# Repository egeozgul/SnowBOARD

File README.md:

# SnowBOARD
This open-source prototyping module streamlines embedded system development by eliminating soldering and complex wiring requirements. The module features dedicated connectors and ports that enable plug-and-play peripheral connections through simple socket interfaces, dramatically reducing setup time and complexity.

Key features include an integrated SD card slot for data storage, a comprehensive battery power management circuit for portable applications, a USB Type-C interface for modern connectivity, and a built-in USB-to-UART converter that simplifies debugging and firmware uploads. This design approach makes embedded prototyping more accessible while maintaining professional-grade functionality for developers at all skill levels.

<p align="center">

</p>

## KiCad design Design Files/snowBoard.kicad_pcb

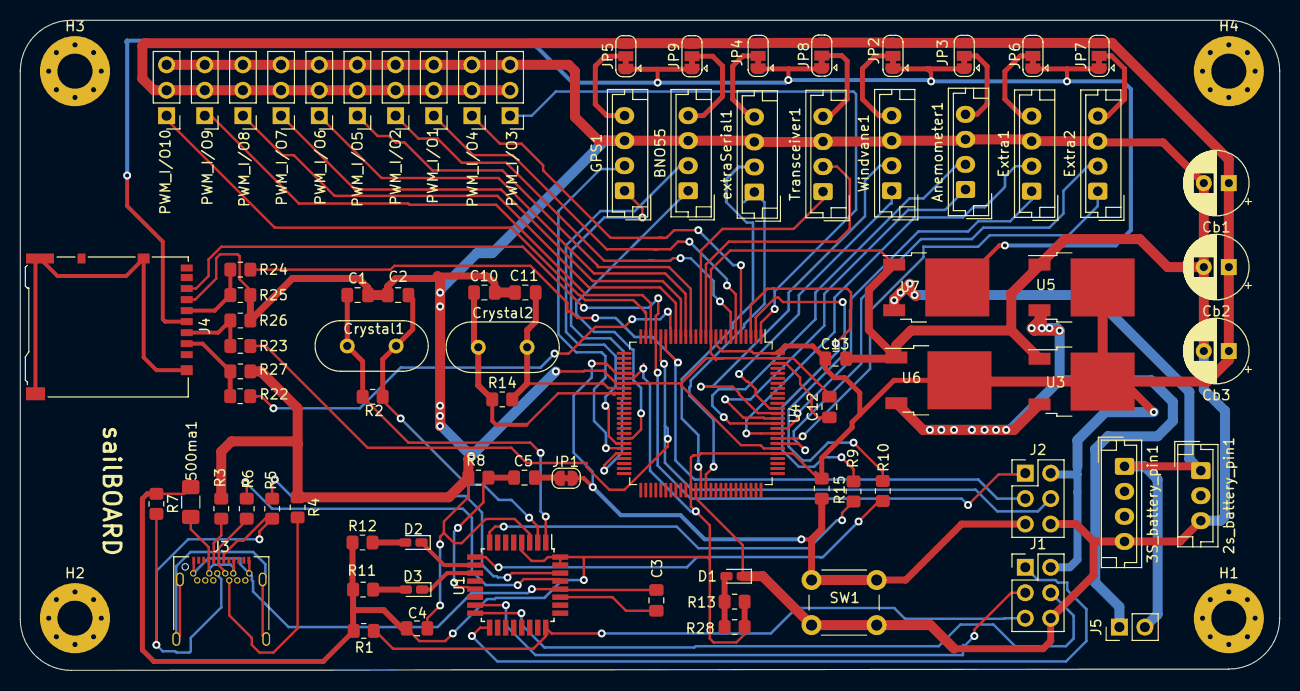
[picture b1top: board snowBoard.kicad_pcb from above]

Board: 2 copper layers, 125.7 x 64.9 mm, 85 parts (0 on the bottom side), 76 nets.

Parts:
2s_battery_pin1: Conn_01x03; JST_EH_B3B-EH-A_1x03_P2.50mm_Vertical
3S_battery_pin1: Conn_01x04; JST_EH_B4B-EH-A_1x04_P2.50mm_Vertical
500ma1: Fuse; Fuse_1206_3216Metric_Pad1.42x1.75mm_HandSolder
Anemometer1: Conn_01x04; JST_EH_B4B-EH-A_1x04_P2.50mm_Vertical
BNO55: Conn_01x04; JST_EH_B4B-EH-A_1x04_P2.50mm_Vertical
C1, C2, C10, C11: 22p; C_0805_2012Metric_Pad1.18x1.45mm_HandSolder
C3: 1u; C_0805_2012Metric_Pad1.18x1.45mm_HandSolder
C4, C5, C12, C13: 100nF; C_0805_2012Metric_Pad1.18x1.45mm_HandSolder
Cb1, Cb2, Cb3: 100uF; CP_Radial_D6.3mm_P2.50mm
Crystal1, Crystal2: 16mhz; Crystal_HC49-U_Vertical
D1, D2, D3: greenLED; LED_0603_1608Metric_Castellated
Extra1, Extra2: Conn_01x04; JST_EH_B4B-EH-A_1x04_P2.50mm_Vertical
GPS1: Conn_01x04; JST_EH_B4B-EH-A_1x04_P2.50mm_Vertical
H1, H2, H3, H4: O; MountingHole_3.5mm_Pad_Via
J1, J2: Conn_02x03_Odd_Even; PinHeader_2x03_P2.54mm_Vertical
J3: USB_C_Receptacle; USB_C_Receptacle_Amphenol_12401548E4-2A
J4: Micro_SD_Card_Det_Hirose_DM3AT; microSD_HC_Hirose_DM3AT-SF-PEJM5
J5: Conn_01x02; PinHeader_1x02_P2.54mm_Vertical
JP1: SolderJumper_2_Bridged; SolderJumper-2_P1.3mm_Bridged_RoundedPad1.0x1.5mm
JP2, JP3, JP4, JP5, JP6, JP7, JP8, JP9: SolderJumper_3_Bridged12; SolderJumper-3_P1.3mm_Bridged12_RoundedPad1.0x1.5mm
PWM_I/O1, PWM_I/O2, PWM_I/O3, PWM_I/O4, PWM_I/O5, PWM_I/O6, PWM_I/O7, PWM_I/O8, PWM_I/O9, PWM_I/O10: Conn_01x03; PinHeader_1x03_P2.54mm_Vertical
R1, R3, R4, R8, R15: 10K; R_0805_2012Metric_Pad1.20x1.40mm_HandSolder
R2, R14: 27; R_0805_2012Metric_Pad1.20x1.40mm_HandSolder
R5, R6: 22; R_0805_2012Metric_Pad1.20x1.40mm_HandSolder
R7, R9, R10, R11, R12, R13, R28: 1K; R_0805_2012Metric_Pad1.20x1.40mm_HandSolder
R22, R23, R24: 2K; R_0805_2012Metric_Pad1.20x1.40mm_HandSolder
R25, R26, R27: 3K; R_0805_2012Metric_Pad1.20x1.40mm_HandSolder
SW1: SW_MEC_5E; SW_PUSH_6mm_H13mm
Transceiver1: Conn_01x04; JST_EH_B4B-EH-A_1x04_P2.50mm_Vertical
U1: ATmega8U2-AU; TQFP-32_7x7mm_P0.8mm
U3, U5, U6: NCP1117-5.0_TO252; TO-252-2
U4: ATmega2560-16AU; TQFP-100_14x14mm_P0.5mm
U7: NCP1117-3.3_TO252; TO-252-2
Windvane1: Conn_01x04; JST_EH_B4B-EH-A_1x04_P2.50mm_Vertical
extraSerial1: Conn_01x04; JST_EH_B4B-EH-A_1x04_P2.50mm_Vertical

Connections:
8U2_MISO: J1.1, U1.17
8U2_MOSI: J1.4, U1.16
8U2_RESET: J1.5, R1.2, U1.24
8U2_SCK: J1.3, U1.15
8U2_XTAL1: C1.1, Crystal1.1, R2.1, U1.1
8U2_XTAL2: C2.1, Crystal1.2, R2.2, U1.2
2560_CS: R22.1, U4.19
2560_MISO: J2.1, J4.7, U4.22
2560_MOSI: J2.4, R23.1, U4.21
2560_RESET: J2.5, JP1.1, R15.1, SW1.1, SW1.2, U4.30
2560_SCK: J2.3, R24.1, U4.20
2560_SCL: BNO55.1, U4.43
2560_SDA: BNO55.2, U4.44
+3V3: J4.4, JP2.1, JP3.1, JP4.1, JP5.1, JP6.1, JP7.1, JP8.1, JP9.1, U7.2
GND: 2s_battery_pin1.3, 3S_battery_pin1.4, Anemometer1.3, BNO55.3, C1.2, C2.2, C4.1, C10.1, C11.1, C12.2, C13.1, Cb1.2, Cb2.2, Cb3.2, D1.1, Extra1.3, Extra2.3, GPS1.3, J1.6, J2.6, J4.6, PWM_I/O1.3, PWM_I/O2.3, PWM_I/O3.3, PWM_I/O4.3, PWM_I/O5.3, PWM_I/O6.3, PWM_I/O7.3, PWM_I/O8.3, PWM_I/O9.3, PWM_I/O10.3, R3.1, R4.1, R8.1, R25.2, R26.2, R27.2, SW1.3, SW1.4, Transceiver1.3, U1.3, U3.1, U4.11, U4.32, U4.62, U4.81, U4.99, U5.1, U6.1, U7.1, Windvane1.3, extraSerial1.3
GPSrx: GPS1.1, U4.46
GPStx: GPS1.2, U4.45
Int0_A: U4.89, Windvane1.1
Int0_B: U4.88, Windvane1.2
Int1_A: Anemometer1.1, U4.87
Int1_B: Anemometer1.2, U4.86
Int2_A: Extra1.1, U4.85
Int2_B: Extra1.2, U4.84
Int3_A: Extra2.1, U4.83
Int3_B: Extra2.2, U4.82
unnamed: 2s_battery_pin1.1, 3S_battery_pin1.1, J5.2, U7.3
unnamed: 500ma1.2, J3.A4, J3.A9, J3.B4, J3.B9
unnamed: Anemometer1.4, JP3.2
unnamed: BNO55.4, JP9.2
unnamed: C3.1, U1.27
unnamed: C5.1, JP1.2
unnamed: C5.2, R8.2, U1.13
unnamed: C12.1, U4.98
unnamed: D1.2, R13.1, R28.2
unnamed: D2.1, U1.10
unnamed: D2.2, R12.2
unnamed: D3.1, U1.11
unnamed: D3.2, R11.2
unnamed: Extra1.4, JP6.2
unnamed: Extra2.4, JP7.2
unnamed: GPS1.4, JP5.2
unnamed: J3.A5, R3.2
unnamed: J3.A6, J3.B6, R6.2
unnamed: J3.A7, J3.B7, R5.2, R7.2
unnamed: J3.B5, R4.2
unnamed: J4.2, R22.2, R27.1
unnamed: J4.3, R23.2, R26.1
unnamed: J4.5, R24.2, R25.1
unnamed: J5.1, U3.3, U5.3, U6.3
unnamed: JP2.2, Windvane1.4
unnamed: JP4.2, extraSerial1.4
unnamed: JP8.2, Transceiver1.4
unnamed: R9.2, U1.8
unnamed: R10.2, U1.9
PWM0: PWM_I/O1.1, U4.6
PWM1: PWM_I/O2.1, U4.7
PWM2: PWM_I/O3.1, U4.1
PWM3: PWM_I/O4.1, U4.5
PWM4: PWM_I/O5.1, U4.15
PWM5: PWM_I/O6.1, U4.16
PWM6: PWM_I/O7.1, U4.17
PWM7: PWM_I/O8.1, U4.18
PWM8: PWM_I/O9.1, U4.23
PWM9: PWM_I/O10.1, U4.24
ProgrammerRx: R9.1, U4.3
ProgrammerTx: R10.1, U4.2
USB_D+: R6.1, U1.29
USB_D-: R5.1, U1.30
USB_VIN: 500ma1.1, C4.2, C13.2, Cb1.1, Cb2.1, Cb3.1, J1.2, J2.2, JP2.3, JP3.3, JP4.3, JP5.3, JP6.3, JP7.3, JP8.3, JP9.3, PWM_I/O1.2, PWM_I/O2.2, PWM_I/O3.2, PWM_I/O4.2, PWM_I/O5.2, PWM_I/O6.2, PWM_I/O7.2, PWM_I/O8.2, PWM_I/O9.2, PWM_I/O10.2, R1.1, R7.1, R11.1, R12.1, R13.2, R15.2, R28.1, U1.4, U1.31, U1.32, U3.2, U4.10, U4.31, U4.61, U4.80, U4.100, U5.2, U6.2
atmega2560_clockPinA: C11.2, Crystal2.2, R14.2, U4.33
atmega2560_clockPinB: C10.2, Crystal2.1, R14.1, U4.34
extraRX: U4.64, extraSerial1.1
extraTX: U4.63, extraSerial1.2
usb_ground: C3.2, J3.A1, J3.A12, J3.B1, J3.B12, U1.28
wireless_rx: Transceiver1.1, U4.13
wireless_tx: Transceiver1.2, U4.12
